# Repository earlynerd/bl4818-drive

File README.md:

# bl4818-drive
replacement integrated servo drive PCB for 4818/4825 brushless motors

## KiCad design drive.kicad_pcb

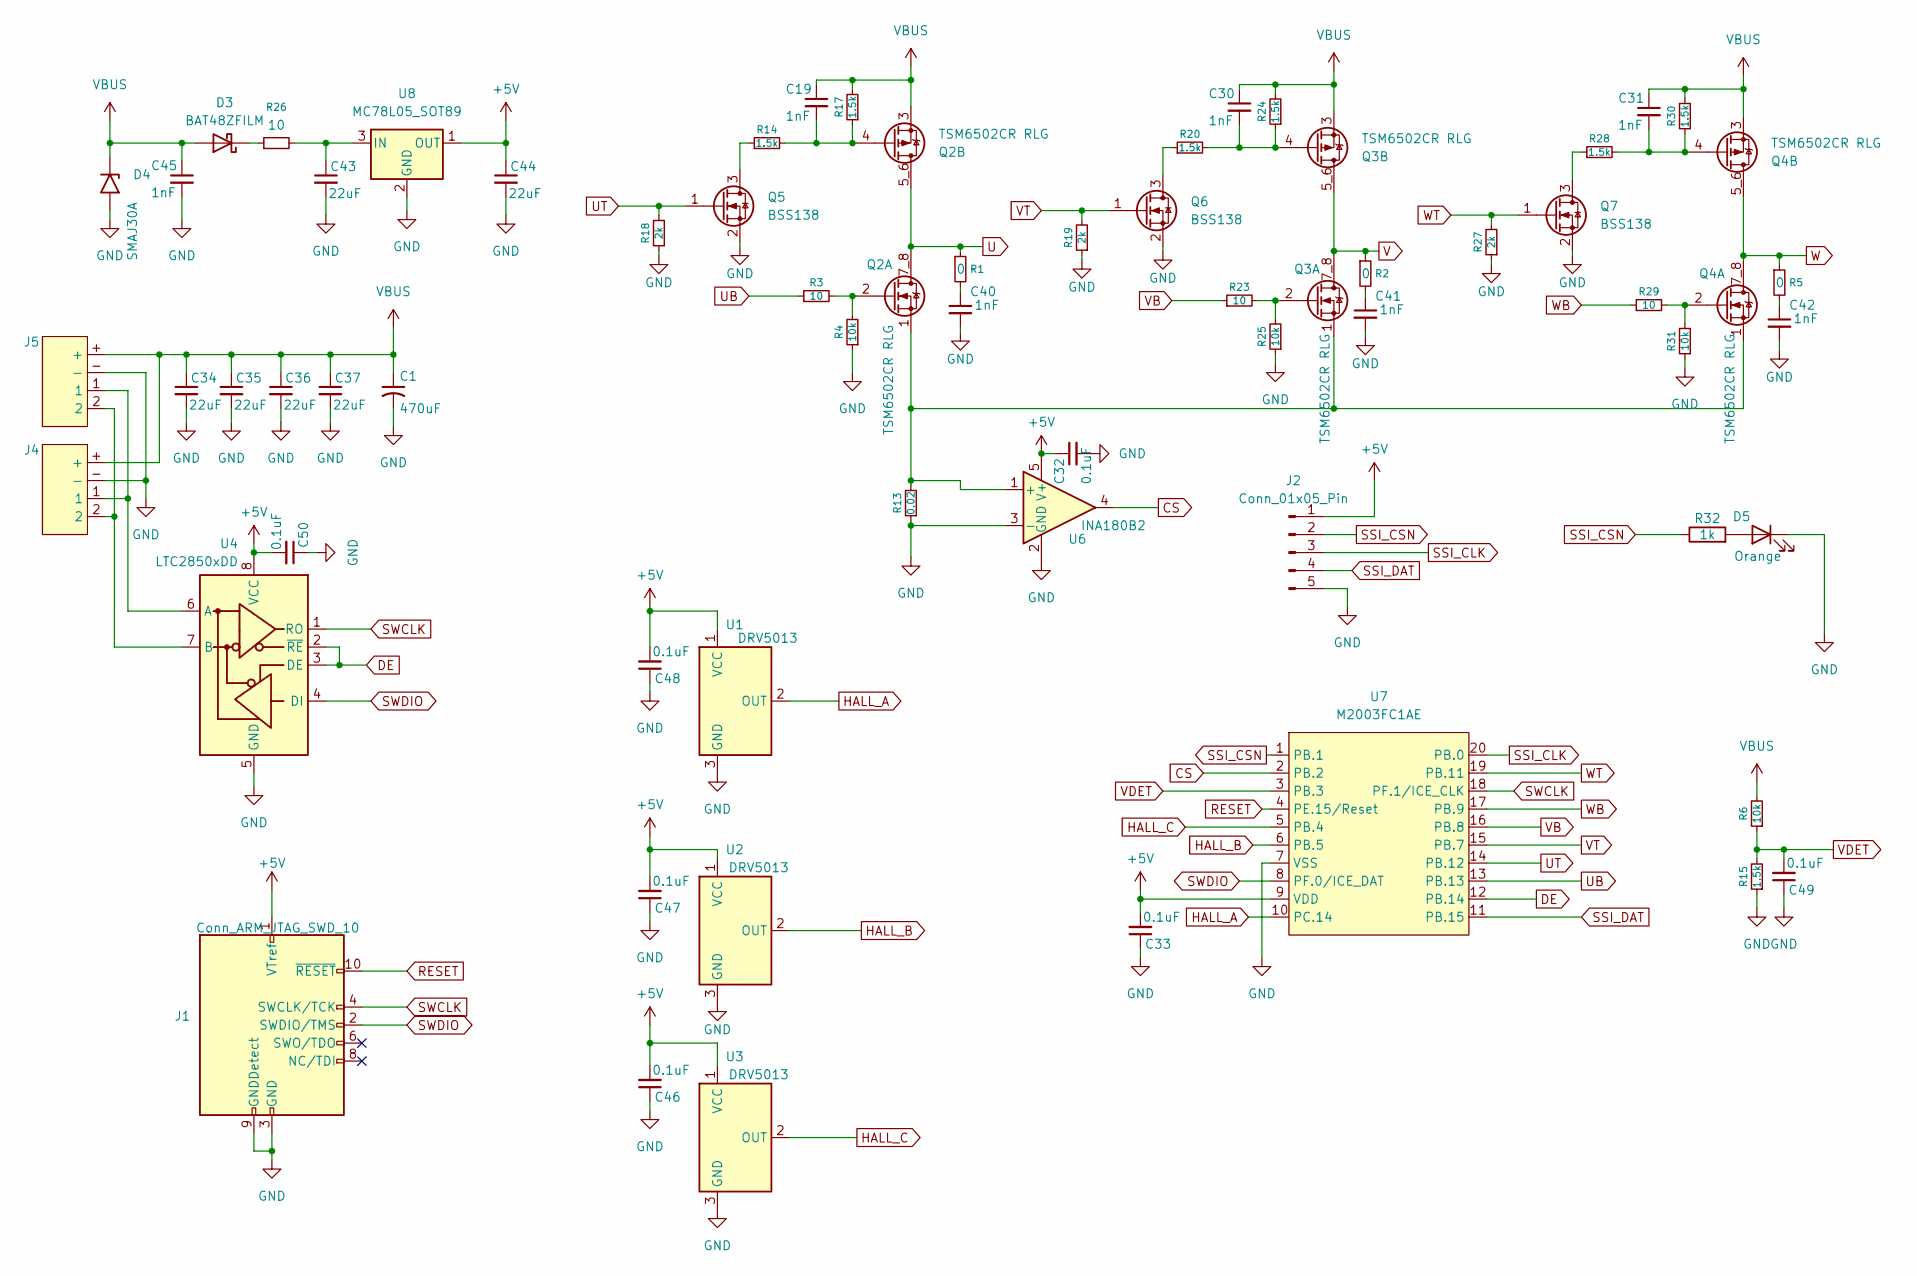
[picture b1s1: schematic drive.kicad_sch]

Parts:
C1: 470uF; C_Radial_D8.0mm_H7.0mm_P3.50mm
C19, C30, C31, C40, C41, C42, C45: 1nF; C_0402_1005Metric
C32, C33, C46, C47, C48, C49, C50: 0.1uF; C_0402_1005Metric
C34, C35, C36, C37, C43, C44: 22uF; C_0805_2012Metric
D3: BAT48ZFILM; D_SOD-123
D4: SMAJ30A; D_SMA
D5: Orange; LED_0603_1608Metric; MPN LTST-C190KFKT
J1: Conn_ARM_JTAG_SWD_10; SAMTEC_FTSH-105-XX-X-DV
J2: Conn_01x05_Pin; PinHeader_1x05_P2.54mm_Vertical
J4, J5: XT30(2+2)PB-M.G.B
Q2, Q3, Q4: TSM6502CR RLG; TRANS_TSM6502CR_RLG
Q5, Q6, Q7: BSS138; SOT-23
R1, R2, R5: 0; R_0603_1608Metric
R3, R23, R29: 10; R_0603_1608Metric
R4, R6, R25, R31: 10k; R_0402_1005Metric
R13: 0.02; R_0805_2012Metric
R14, R15, R17, R20, R24, R28, R30: 1.5k; R_0402_1005Metric
R18, R19, R27: 2k; R_0402_1005Metric
R26: 10; R_0805_2012Metric
R32: 1k; R_0402_1005Metric; MPN RC0402FR-071KL
U1, U2, U3: DRV5013; SOT-23
U4: LTC2850xDD; DFN-8-1EP_3x3mm_P0.5mm_EP1.66x2.38mm
U6: INA180B2; SOT-23-5
U7: M2003FC1AE; TSSOP-20_4.4x6.5mm_P0.65mm
U8: MC78L05_SOT89; SOT-89-3

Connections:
+5V: C32.1, C33.2, C44.1, C46.2, C47.2, C48.2, C50.2, J1.1 (VTref), J2.1, U1.1 (VCC), U2.1 (VCC), U3.1 (VCC), U4.8 (VCC), U6.5 (V+), U7.9 (VDD), U8.1 (OUT)
CS: U6.4, U7.2 (PB.2)
DE: U4.2 (~RE), U4.3 (DE), U7.12 (PB.14)
GND: C1.2, C32.2, C33.1, C34.2, C35.2, C36.2, C37.2, C40.2, C41.2, C42.2, C43.2, C44.2, C45.2, C46.1, C47.1, C48.1, C49.1, C50.1, D4.2 (A2), D5.1 (K), J1.3 (GND), J1.5 (GND), J1.9 (GNDDetect), J2.5, J4.-, J5.-, Q5.2 (S), Q6.2 (S), Q7.2 (S), R4.1, R13.1, R15.1, R18.1, R19.1, R25.1, R27.1, R31.1, U1.3 (GND), U2.3 (GND), U3.3 (GND), U4.5 (GND), U4.9 (GND), U6.2 (GND), U6.3 (-), U7.7 (VSS), U8.2 (GND)
HALL_A: U1.2 (OUT), U7.10 (PC.14)
HALL_B: U2.2 (OUT), U7.6 (PB.5)
HALL_C: U3.2 (OUT), U7.5 (PB.4)
unnamed: C40.1, R1.2
unnamed: C41.1, R2.2
unnamed: C42.1, R5.2
unnamed: D3.1 (K), R26.1
unnamed: D5.2 (A), R32.2
unnamed: Q2.2 (G1), R3.2, R4.2
unnamed: Q2.1 (S1), Q3.1 (S1), Q4.1 (S1), R13.2, U6.1 (+)
unnamed: C19.2, Q2.4 (G2), R14.2, R17.1
unnamed: Q3.2 (G1), R23.2, R25.2
unnamed: C30.2, Q3.4 (G2), R20.2, R24.1
unnamed: Q4.2 (G1), R29.2, R31.2
unnamed: C31.2, Q4.4 (G2), R28.2, R30.1
unnamed: Q5.3 (D), R14.1
unnamed: Q6.3 (D), R20.1
unnamed: Q7.3 (D), R28.1
unnamed: J4.1, J5.1, U4.6 (A)
unnamed: J4.2, J5.2, U4.7 (B)
unnamed: C43.1, R26.2, U8.3 (IN)
RESET: J1.10 (~RESET), U7.4 (PE.15/Reset)
SSI_CLK: J2.3, U7.20 (PB.0)
SSI_CSN: J2.2, R32.1, U7.1 (PB.1)
SSI_DAT: J2.4, U7.11 (PB.15)
SWCLK: J1.4 (SWCLK/TCK), U4.1 (RO), U7.18 (PF.1/ICE_CLK)
SWDIO: J1.2 (SWDIO/TMS), U4.4 (DI), U7.8 (PF.0/ICE_DAT)
U: Q2.5_6 (D2), Q2.7_8 (D1), R1.1
UB: R3.1, U7.13 (PB.13)
UT: Q5.1 (G), R18.2, U7.14 (PB.12)
V: Q3.5_6 (D2), Q3.7_8 (D1), R2.1
VB: R23.1, U7.16 (PB.8)
VBUS: C1.1, C19.1, C30.1, C31.1, C34.1, C35.1, C36.1, C37.1, C45.1, D3.2 (A), D4.1 (A1), J4.+, J5.+, Q2.3 (S2), Q3.3 (S2), Q4.3 (S2), R6.2, R17.2, R24.2, R30.2
VDET: C49.2, R6.1, R15.2, U7.3 (PB.3)
VT: Q6.1 (G), R19.2, U7.15 (PB.7)
W: Q4.5_6 (D2), Q4.7_8 (D1), R5.1
WB: R29.1, U7.17 (PB.9)
WT: Q7.1 (G), R27.2, U7.19 (PB.11)

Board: 2 copper layers, 64 parts (3 on the bottom side), 42 nets, no tracks yet.

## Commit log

2026-05-14 m2003 drive
2026-05-15 schematic complete
2026-05-15 add gitignore
2026-05-15 progress
2026-05-20 pcb progress
